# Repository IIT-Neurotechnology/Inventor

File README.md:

# Headframe Federico

# Miniscope baseplate
 Baseplate miniscopio in Ergal per accoppiamento foro albero con una lente cilindrica GRIN che verra successivamente incollata per fissare l'accoppiamento.

# Load cells 

# Headframe_Edit (from Allen institute)

# Luigi's servos setup

# Chronic Neuropixels probes stack

# Laser controller Ephys circuit

# Thermocouple breathing circuit

# Probe mounting railguide (Edited from NP2)

# Virmen based VR tapis roulant 

# Behavioral cage

# IMU 9DOF

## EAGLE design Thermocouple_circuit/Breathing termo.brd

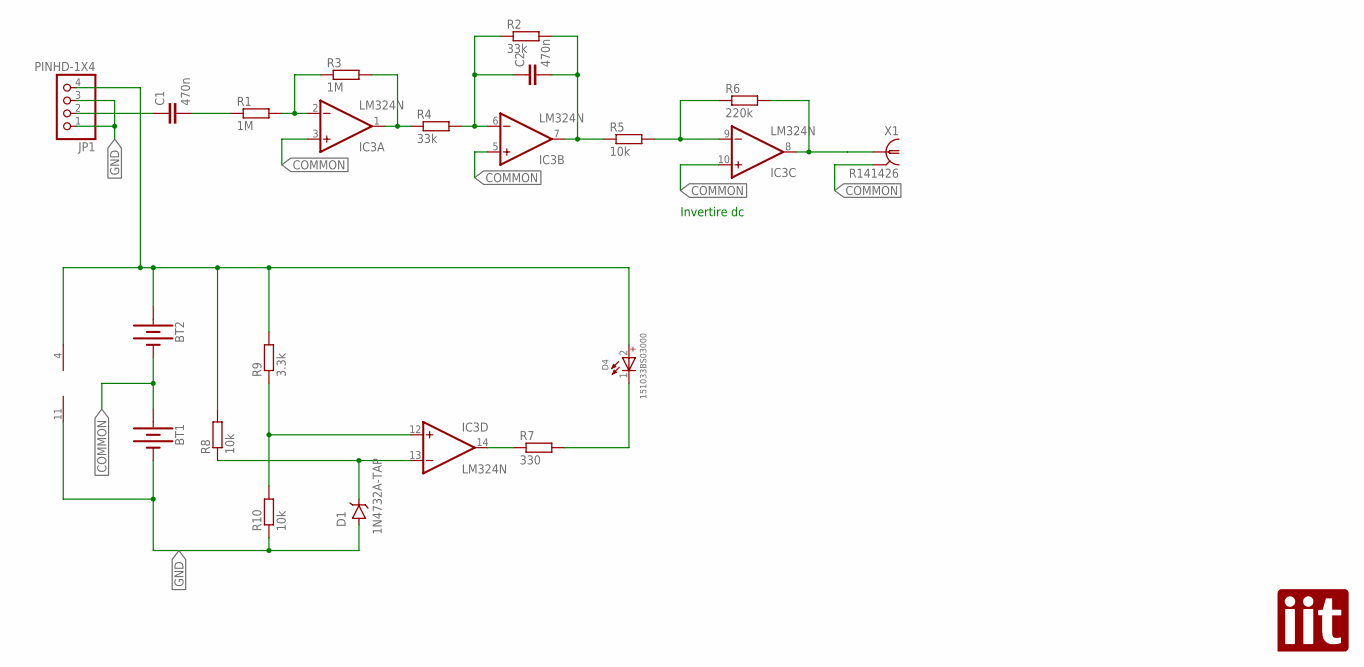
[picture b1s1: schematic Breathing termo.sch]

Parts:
BT1, BT2: BATTERY-9V; BATTCON_9V
C1, C2: 470n; C025-025X050
D1: 1N4732A-TAP; DO-41
D4: 151033BS03000; WL-TMRW_3MM_STOPPER
IC3: LM324N; DIL14
JP1: PINHD-1X4; 1X04
R1, R3: 1M; 0204/7
R2, R4: 33k; 0204/7
R5, R8, R10: 10k; 0204/7
R6: 220k; 0204/7
R7: 330; 0204/7
R9: 3.3k; 0204/7
U$1: LOGO; IIT
X1: R141426

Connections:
COMMON: BT1.+, BT2.-, IC3.3 (+IN), IC3.5 (+IN), IC3.10 (+IN), X1.2, X1.3 (2), X1.4 (2), X1.5 (2)
GND: BT1.-, D1.A, IC3.11 (V-), JP1.1, JP1.3, R10.1
unnamed: C1.2, R1.1
unnamed: IC3.2 (-IN), R1.2, R3.1
unnamed: IC3.1 (OUT), R3.2, R4.1
unnamed: C2.1, IC3.6 (-IN), R2.1, R4.2
unnamed: C2.2, IC3.7 (OUT), R2.2, R5.1
unnamed: IC3.9 (-IN), R5.2, R6.1
unnamed: IC3.8 (OUT), R6.2, X1.1
unnamed: IC3.12 (+IN), R9.1, R10.2
unnamed: D4.1 (-), R7.2
unnamed: D1.C, IC3.13 (-IN), R8.1
unnamed: C1.1, JP1.2
unnamed: IC3.14 (OUT), R7.1
unnamed: BT2.+, D4.2 (+), IC3.4 (V+), JP1.4, R8.2, R9.2

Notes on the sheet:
Invertire dc

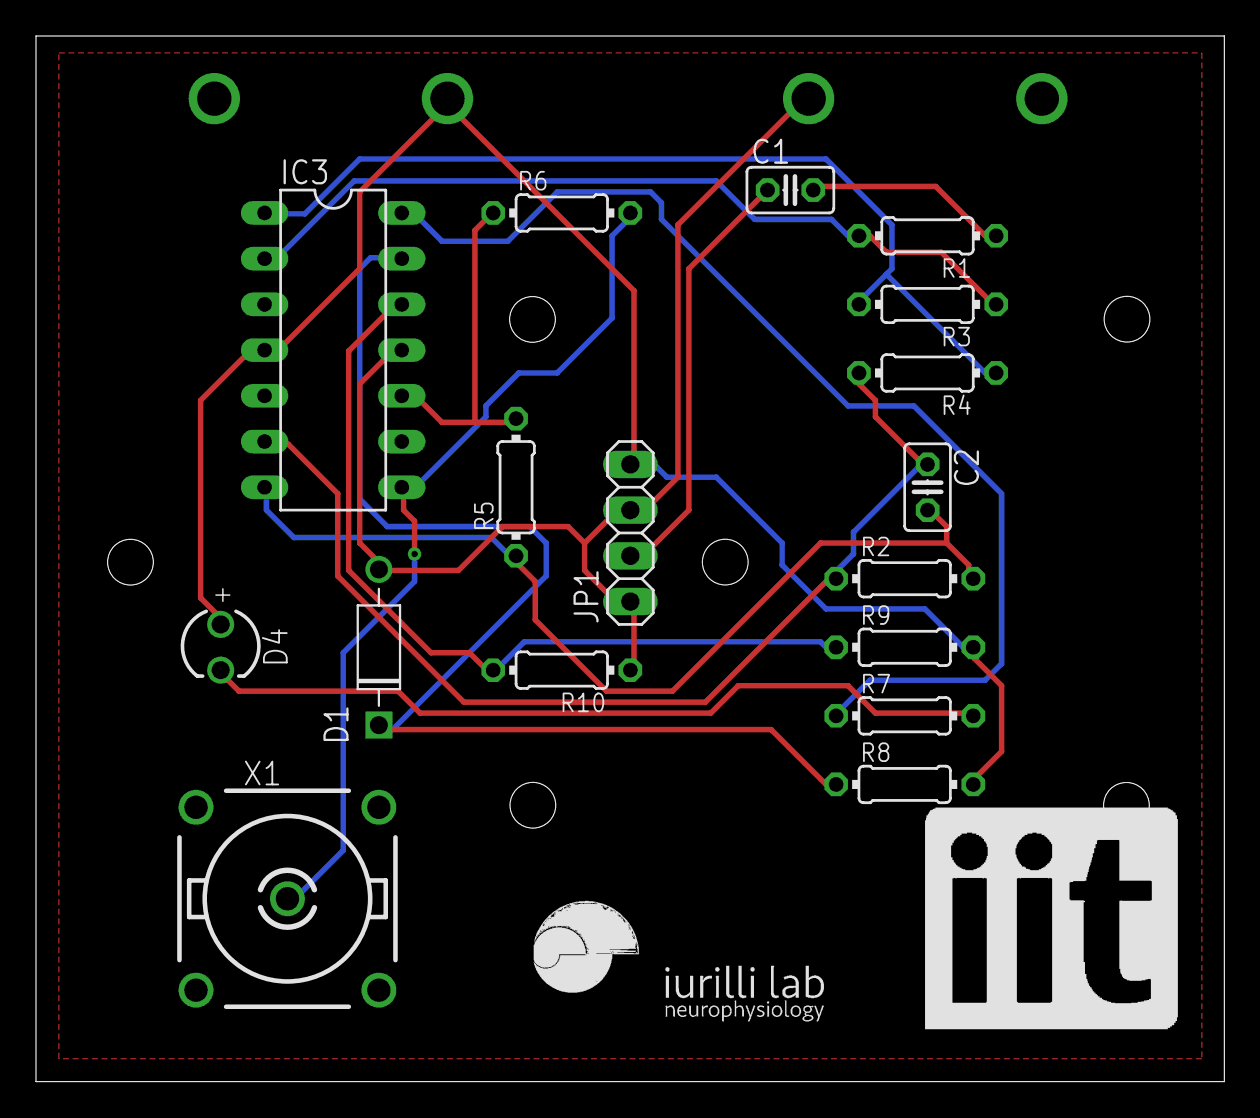
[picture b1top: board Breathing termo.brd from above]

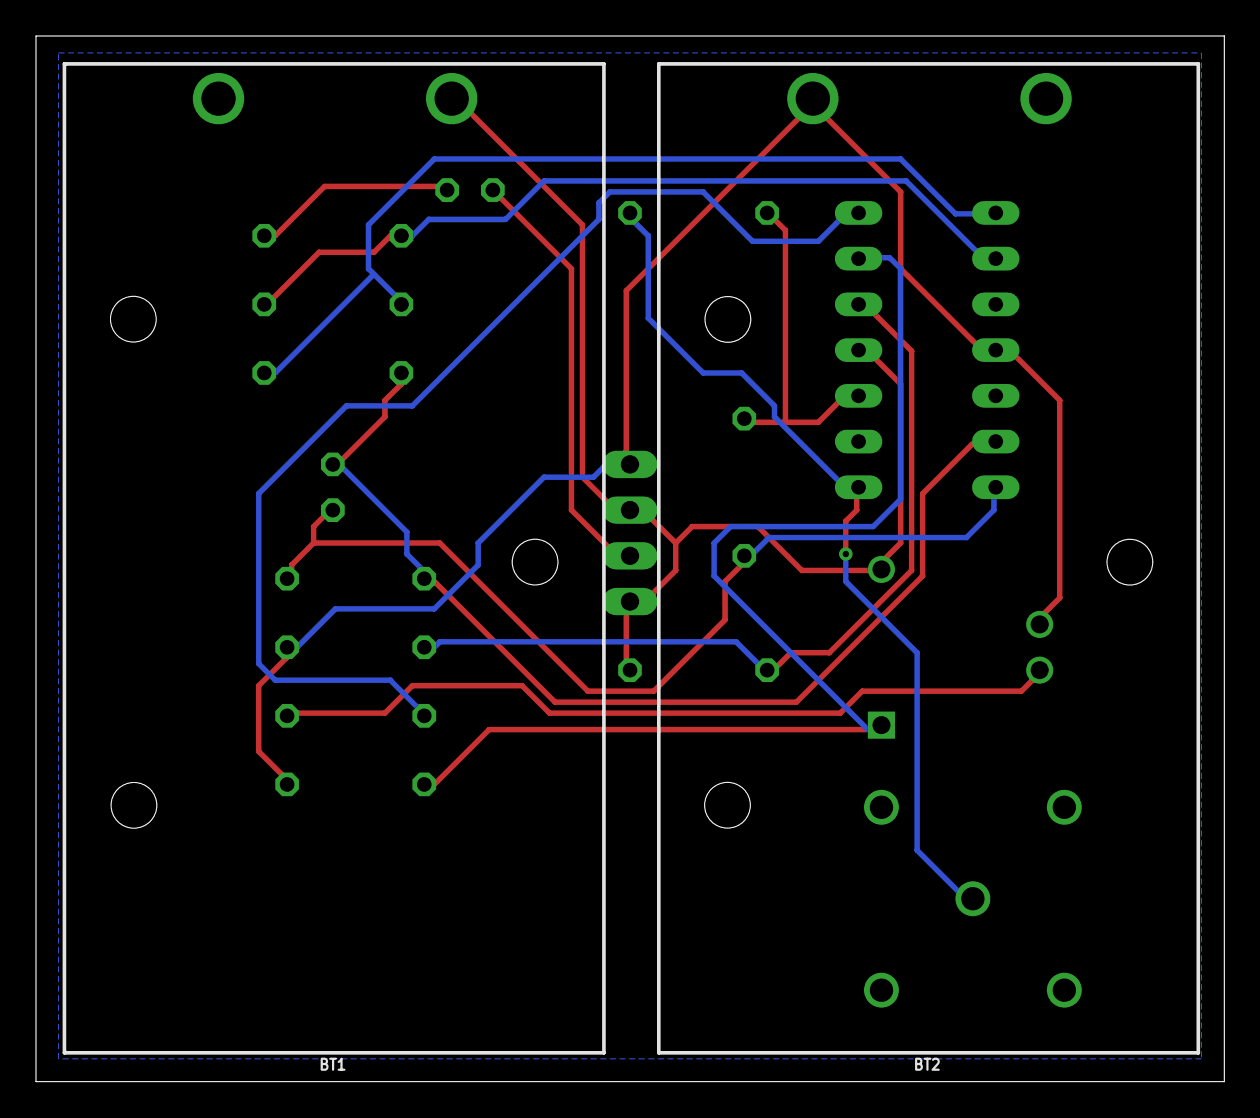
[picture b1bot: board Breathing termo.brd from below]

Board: 2 copper layers, 66.0 x 58.1 mm, 21 parts (2 on the bottom side), 15 nets.

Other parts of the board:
U$2: IURILLI

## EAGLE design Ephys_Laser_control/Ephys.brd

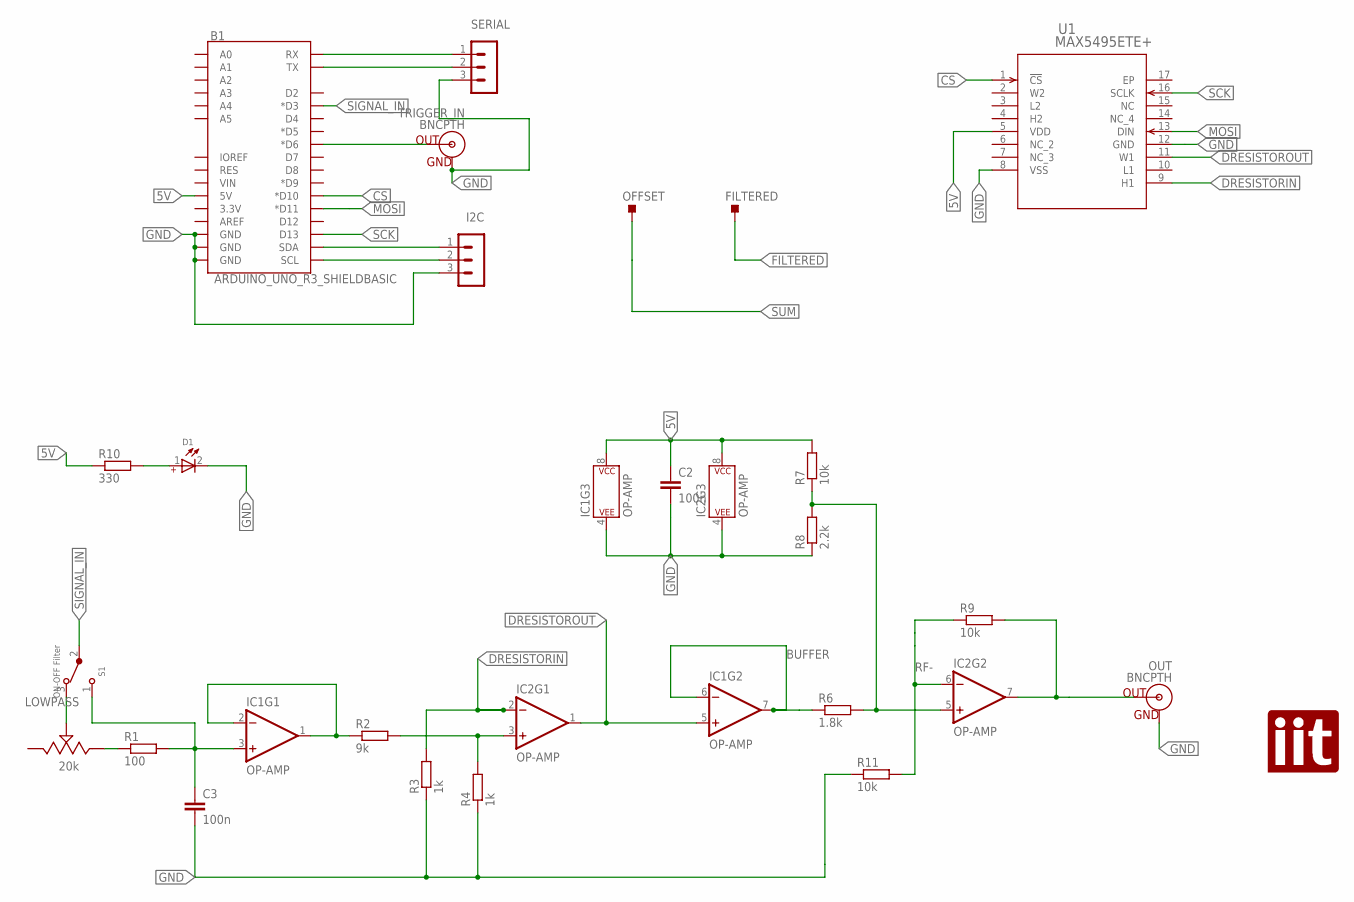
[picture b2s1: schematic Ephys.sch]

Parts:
B1: ARDUINO_UNO_R3_SHIELDBASIC; UNO_R3_SHIELD
C2, C3: 100n; C025-025X050
D1: WL-TMRC_3MM_151031SS04000_WITHOUTSTOPPER; WL-TMRC_3MM
FILTERED: TESTPOINT_TPS-PAD-036; TESTPOINT_PAD-036
I2C: MA03-1
IC1, IC2: OP-AMP; DIP08
LOWPASS: 20k; 3362P-1-103LF
OFFSET: TESTPOINT_TPS-PAD-036; TESTPOINT_PAD-036
OUT: BNCPTH; BNC
R1: 100; 0204/7
R2: 9k; 0204/7
R3, R4: 1k; 0204/7
R6: 1.8k; 0204/7
R7, R9, R11: 10k; 0204/7
R8: 2.2k; 0204/7
R10: 330; 0204/7
S1: ON-OFF Filter; 472121010111
SERIAL: MA03-1
TRIGGER_IN: BNCPTH; BNC
U1: MAX5495ETE+; 21-0140_T1655+3_MXM
U$1: LOGO; IIT

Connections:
5V: B1.5V, C2.1, IC1.8 (P$V+), IC2.8 (P$V+), R7.2, R10.1, U1.5 (VDD)
BUFFER: IC1.6 (-IN), IC1.7 (OUT), R6.1
CS: B1.D10 (*D10), U1.1 (!CS)
DRESISTORIN: IC2.2 (-IN), R3.2, U1.9 (H1)
DRESISTOROUT: IC1.5 (+IN), IC2.1 (OUT), U1.11 (W1)
FILTERED: C3.1, FILTERED.1, IC1.3 (+IN), R1.2, S1.1
GND: B1.GND@0 (GND), B1.GND@1 (GND), B1.GND@2 (GND), C2.2, C3.2, D1.2 (-), I2C.3, IC1.4 (P$V-), IC2.4 (P$V-), OUT.GND, R3.1, R4.1, R8.1, R11.1, SERIAL.3, TRIGGER_IN.GND, U1.8 (VSS), U1.12 (GND)
MOSI: B1.D11 (*D11), U1.13 (DIN)
unnamed: IC1.1 (OUT), IC1.2 (-IN), R2.1
unnamed: IC2.3 (+IN), R2.2, R4.2
unnamed: B1.D6 (*D6), TRIGGER_IN.S (OUT)
unnamed: B1.SDA, I2C.1
unnamed: B1.SCL, I2C.2
unnamed: B1.RX, SERIAL.1
unnamed: LOWPASS.3, R1.1
unnamed: D1.1 (+), R10.2
unnamed: LOWPASS.2, S1.3
unnamed: B1.TX, SERIAL.2
OUT: IC2.7 (OUT), OUT.S (OUT), R9.2
RF-: IC2.6 (-IN), R9.1, R11.2
SCK: B1.D13, U1.16 (SCLK)
SIGNAL_IN: B1.D3 (*D3), S1.2
SUM: IC2.5 (+IN), OFFSET.1, R6.2, R7.1, R8.2

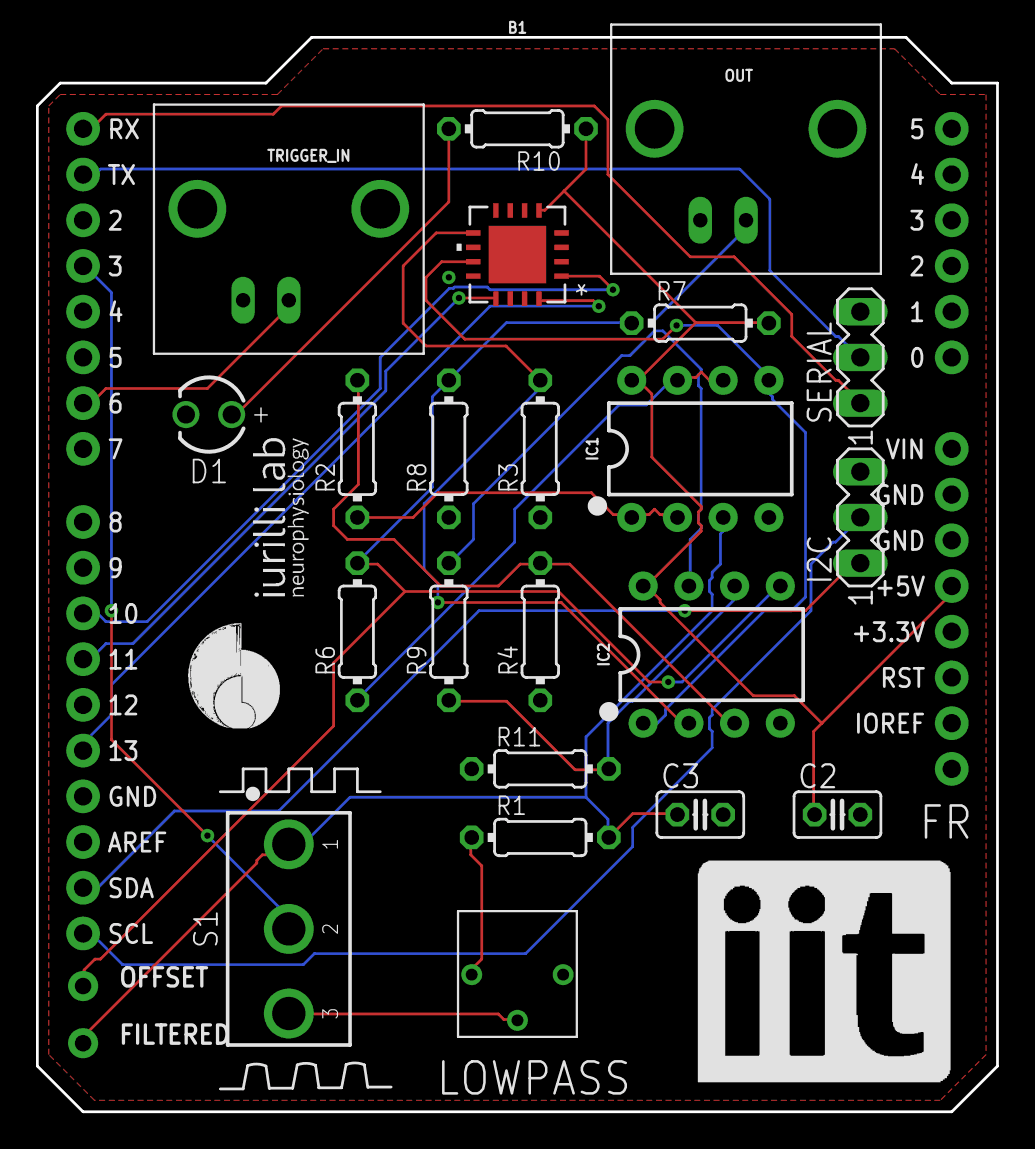
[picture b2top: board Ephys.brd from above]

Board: 2 copper layers, 53.3 x 59.7 mm, 27 parts (0 on the bottom side), 23 nets.

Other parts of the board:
U$2: IURILLI

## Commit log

2024-04-12 Added second bnc and serial breakout
2024-04-17 Commessa aperta
2024-04-17 Rimossi file inutili da fusion
2024-04-18 My designs in
2024-04-22 Second try to Lorenzo
2024-05-03 Headframe sent to workshop
2024-05-07 sent
2024-05-09 Added federico Headframe
2024-05-09 Project Finished
2024-05-17 Breathing corrected, Federico Headframe update
2024-05-17 Updated Names
2024-05-22 Behavioral cage in
2024-05-22 Updated images
2024-05-23 Imu in
2024-07-31 NP2 docker and payloads edits
2024-09-10 Rod Holder IN and rearranged stuff
2026-03-30 NCS_002_003
2026-05-18 May dump
2026-06-03 Eric_probe_holder

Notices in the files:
parts and their libraries:
SparkFun-Boards: Licensing: Creative Commons ShareAlike 4.0 International - https://creativecommons.org/licenses/by-sa/4.0
Wurth_LEDs_WL-TMRC: Copyright: Würth Elektronik
COPYRIGHT: Copyright (C) 2024 Ultra Librarian. All rights reserved.
